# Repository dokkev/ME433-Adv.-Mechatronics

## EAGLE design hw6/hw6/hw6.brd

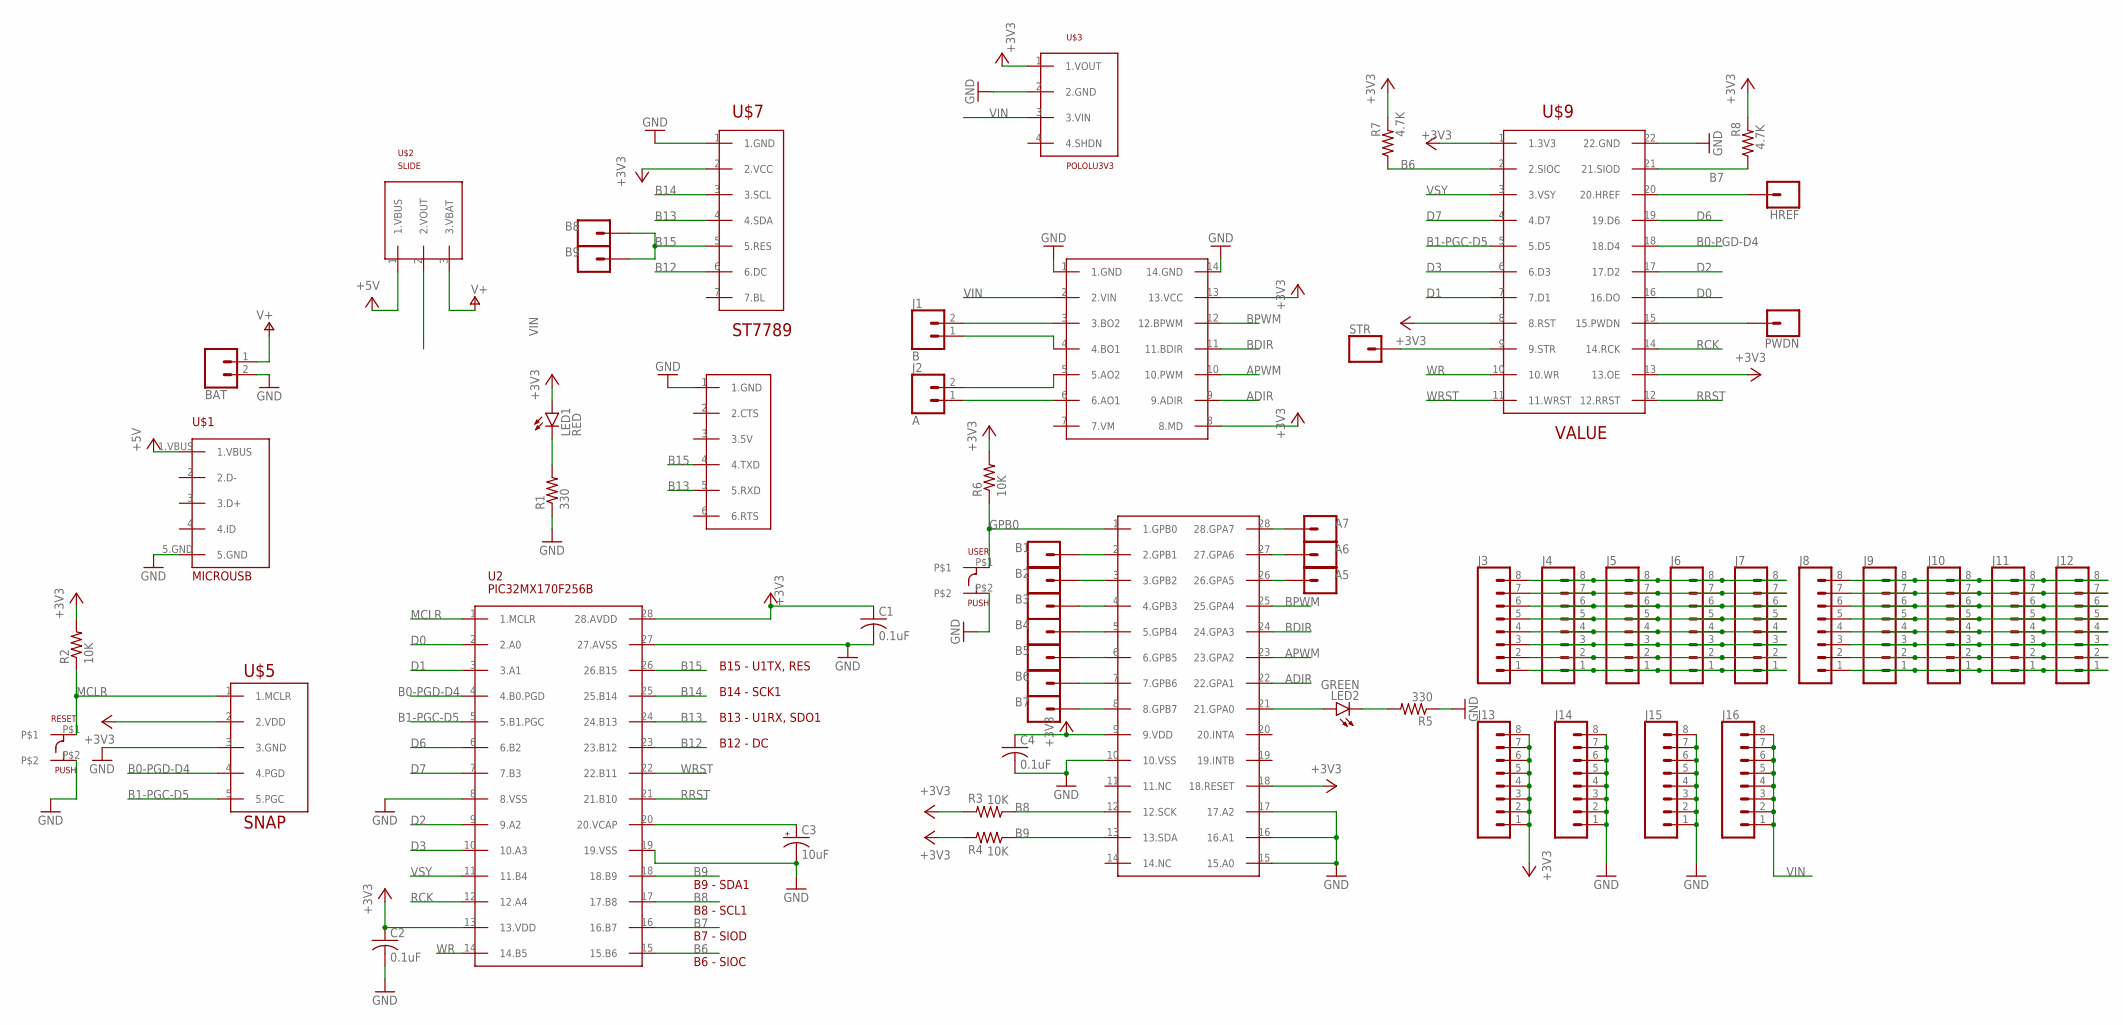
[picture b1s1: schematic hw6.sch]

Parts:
A5, A6, A7: CONN_01; 1X01
B1, B2, B3, B4, B5, B6, B7, B8, B9: CONN_01; 1X01
BAT: CONN_02; 1X02
C1, C2, C4: 0.1uF; C025-030X050
C3: 10uF; B45181B
HREF: CONN_01; 1X01
J1: B; 1X02
J2: A; 1X02
J3, J4, J5, J6, J7, J8, J9, J10, J11, J12, J13, J14, J15, J16: CONN_08"; 1X08
LED1: RED; LED3MM
LED2: GREEN; LED3MM
PWDN: CONN_01; 1X01
R1, R5: 330; 0207/10
R2, R3, R4, R6: 10K; 0207/10
R7, R8: 4.7K; 0207/10
RESET: PUSH
STR: CONN_01; 1X01
U2: PIC32MX170F256B; DIL28-3
U$1: MICROUSB
U$2: SLIDE
U$3: POLOLU3V3
U$4: DRV8835
U$5: SNAP
U$6: CP2104_FRIEND
U$7: ST7789
U$8: MCP23017; DIL28-3
U$9: OV7670FIFO
USER: PUSH

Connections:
+3V3: C1.1, C2.1, C4.1, J13.1, J13.2, J13.3, J13.4, J13.5, J13.6, J13.7, J13.8, LED1.A, R2.2, R3.2, R4.2, R6.2, R7.2, R8.2, U2.13 (13.VDD), U2.28 (28.AVDD), U$3.1 (1.VOUT), U$4.8 (8.MD), U$4.13 (13.VCC), U$5.2 (2.VDD), U$7.2 (2.VCC), U$8.9 (9.VDD), U$8.18 (18.RESET), U$9.1 (1.3V3), U$9.8 (8.RST), U$9.13 (13.OE)
+5V: U$1.1.VBUS, U$2.1 (1.VBUS)
ADIR: U$4.9 (9.ADIR), U$8.22 (22.GPA1)
APWM: U$4.10 (10.PWM), U$8.23 (23.GPA2)
B0-PGD-D4: U2.4 (4.B0.PGD), U$5.4 (4.PGD), U$9.18 (18.D4)
B1-PGC-D5: U2.5 (5.B1.PGC), U$5.5 (5.PGC), U$9.5 (5.D5)
B6: R7.1, U2.15 (15.B6), U$9.2 (2.SIOC)
B7: R8.1, U2.16 (16.B7), U$9.21 (21.SIOD)
B8: R3.1, U2.17 (17.B8), U$8.12 (12.SCK)
B9: R4.1, U2.18 (18.B9), U$8.13 (13.SDA)
B12: U2.23 (23.B12), U$7.6 (6.DC)
B13: U2.24 (24.B13), U$6.5 (5.RXD), U$7.4 (4.SDA)
B14: U2.25 (25.B14), U$7.3 (3.SCL)
B15: B8.1, B9.1, U2.26 (26.B15), U$6.4 (4.TXD), U$7.5 (5.RES)
BDIR: U$4.11 (11.BDIR), U$8.24 (24.GPA3)
BPWM: U$4.12 (12.BPWM), U$8.25 (25.GPA4)
D0: U2.2 (2.A0), U$9.16 (16.DO)
D1: U2.3 (3.A1), U$9.7 (7.D1)
D2: U2.9 (9.A2), U$9.17 (17.D2)
D3: U2.10 (10.A3), U$9.6 (6.D3)
D6: U2.6 (6.B2), U$9.19 (19.D6)
D7: U2.7 (7.B3), U$9.4 (4.D7)
GND: BAT.2, C1.2, C2.2, C3.-, C4.2, J14.1, J14.2, J14.3, J14.4, J14.5, J14.6, J14.7, J14.8, J15.1, J15.2, J15.3, J15.4, J15.5, J15.6, J15.7, J15.8, R1.1, R5.1, RESET.P$2, U2.8 (8.VSS), U2.19 (19.VSS), U2.27 (27.AVSS), U$1.5.GND, U$3.2 (2.GND), U$4.1 (1.GND), U$4.14 (14.GND), U$5.3 (3.GND), U$6.1 (1.GND), U$7.1 (1.GND), U$8.10 (10.VSS), U$8.15 (15.A0), U$8.16 (16.A1), U$8.17 (17.A2), U$9.22 (22.GND), USER.P$2
GPB0: R6.1, U$8.1 (1.GPB0), USER.P$1
MCLR: R2.1, RESET.P$1, U2.1 (1.MCLR), U$5.1 (1.MCLR)
unnamed: LED1.K (C), R1.2
unnamed: C3.+, U2.20 (20.VCAP)
unnamed: LED2.K (C), R5.2
unnamed: LED2.A, U$8.21 (21.GPA0)
unnamed: J1.2, U$4.3 (3.BO2)
unnamed: J1.1, U$4.4 (4.BO1)
unnamed: J2.2, U$4.5 (5.AO2)
unnamed: J2.1, U$4.6 (6.AO1)
unnamed: STR.1, U$9.9 (9.STR)
unnamed: HREF.1, U$9.20 (20.HREF)
unnamed: PWDN.1, U$9.15 (15.PWDN)
unnamed: B1.1, U$8.2 (2.GPB1)
unnamed: B2.1, U$8.3 (3.GPB2)
unnamed: B3.1, U$8.4 (4.GPB3)
unnamed: B4.1, U$8.5 (5.GPB4)
unnamed: B5.1, U$8.6 (6.GPB5)
unnamed: B6.1, U$8.7 (7.GPB6)
unnamed: B7.1, U$8.8 (8.GPB7)
unnamed: A7.1, U$8.28 (28.GPA7)
unnamed: A6.1, U$8.27 (27.GPA6)
unnamed: A5.1, U$8.26 (26.GPA5)
unnamed: J3.8, J4.8, J5.8, J6.8, J7.8
unnamed: J3.7, J4.7, J5.7, J6.7, J7.7
unnamed: J3.6, J4.6, J5.6, J6.6, J7.6
unnamed: J3.5, J4.5, J5.5, J6.5, J7.5
unnamed: J3.4, J4.4, J5.4, J6.4, J7.4
unnamed: J3.3, J4.3, J5.3, J6.3, J7.3
unnamed: J3.2, J4.2, J5.2, J6.2, J7.2
unnamed: J3.1, J4.1, J5.1, J6.1, J7.1
unnamed: J8.8, J9.8, J10.8, J11.8, J12.8
unnamed: J8.7, J9.7, J10.7, J11.7, J12.7
unnamed: J8.6, J9.6, J10.6, J11.6, J12.6
unnamed: J8.5, J9.5, J10.5, J11.5, J12.5
unnamed: J8.4, J9.4, J10.4, J11.4, J12.4
unnamed: J8.3, J9.3, J10.3, J11.3, J12.3
unnamed: J8.2, J9.2, J10.2, J11.2, J12.2
unnamed: J8.1, J9.1, J10.1, J11.1, J12.1
RCK: U2.12 (12.A4), U$9.14 (14.RCK)
RRST: U2.21 (21.B10), U$9.12 (12.RRST)
V+: BAT.1, U$2.3 (3.VBAT)
VIN: J16.1, J16.2, J16.3, J16.4, J16.5, J16.6, J16.7, J16.8, U$2.2 (2.VOUT), U$3.3 (3.VIN), U$4.2 (2.VIN)
VSY: U2.11 (11.B4), U$9.3 (3.VSY)
WR: U2.14 (14.B5), U$9.10 (10.WR)
WRST: U2.22 (22.B11), U$9.11 (11.WRST)

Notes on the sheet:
B15 - U1TX, RES
B13 - U1RX, SDO1
B14 - SCK1
B12 - DC
B9 - SDA1
B8 - SCL1
B7 - SIOD
B6 - SIOC

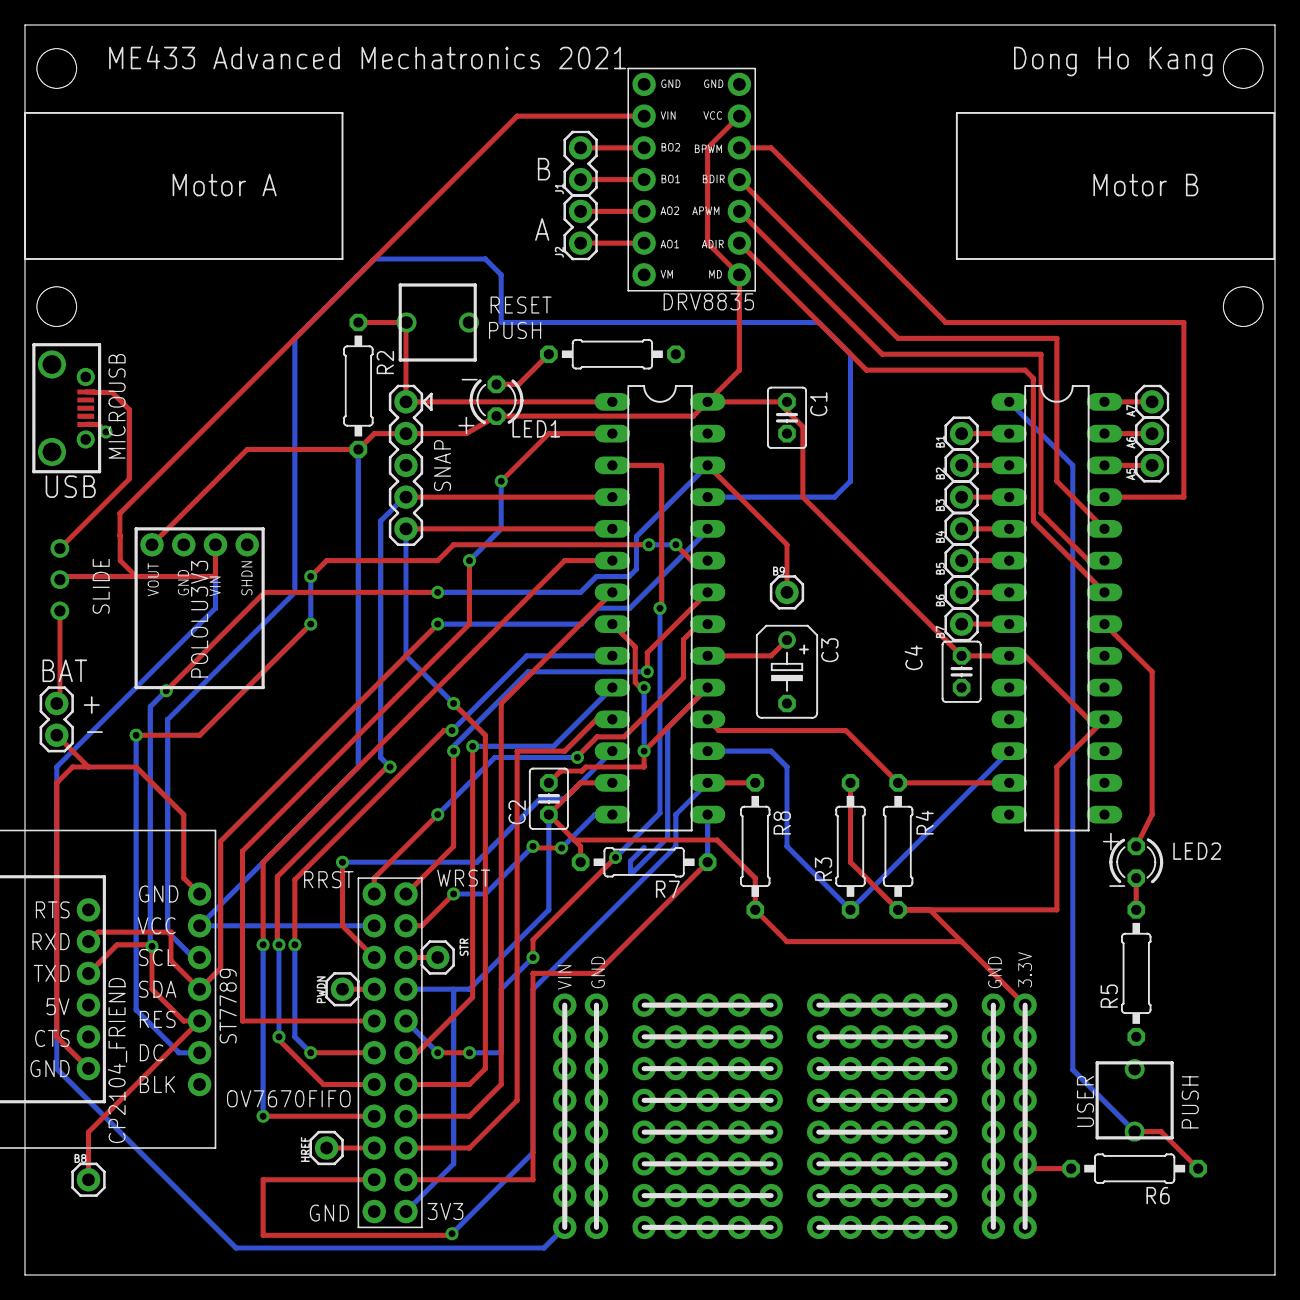
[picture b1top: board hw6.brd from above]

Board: 2 copper layers, 100.0 x 100.0 mm, 58 parts (1 on the bottom side), 69 nets.

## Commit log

2021-04-06 hw2 added
2021-04-07 question 5
2021-04-09 hw2 posted
2021-04-10 hw3 posted
2021-04-16 hw4 created
2021-04-16 circuit photo
2021-04-16 error fixed
2021-04-16 wrong file
2021-04-18 diagram added
2021-04-24 hw5 added
2021-06-04 disp
2021-06-04 led fixed
2021-06-04 colorful led
2021-06-08 gyro
2021-06-08 eagle
2021-06-08 led fix
